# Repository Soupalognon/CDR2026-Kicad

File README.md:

# Robot CDF 2026

Carte électronique principale du robot **Wall-A**, conçu pour la **Coupe de France de Robotique 2026**.

## Description

Ce PCB regroupe tout ce dont le robot a besoin pour fonctionner :

- **Alimentation** : génère les rails 24 V, 12 V, 5 V et 3,3 V à partir de la batterie
- **Moteurs et actionneurs** : commande des moteurs des roues, des moteurs secondaires et des servomoteurs
- **Capteurs** : encodeurs, capteurs de distance, interrupteurs et sondes de température
- **Contrôle bas niveau** : un microcontrôleur STM32F407 pilote le tout en temps réel
- **Liaison avec le PC embarqué** : USB et Ethernet pour le haut niveau. La prise USB Type-C du PC embarqué est une **sortie d'alimentation 5 V**

### Alimentation

La carte est alimentée par la batterie (LiPo 4S 14.8V, connecteur XT90) avec une tension d'entrée de 16 V à 24 V. Elle génère cinq rails avec trois types de convertisseurs :

| Rail | Type de convertisseur | Composant | Courant | Utilisation |
|---|---|---|---|---|
| 24 V | Élévateur (boost) | Module DC/DC ABB ABXS005 | 5,4 A | Moteurs des roues |
| 12 V | Abaisseur (buck) | TI PTN78020W | 5,8 A | Actionneurs (servomoteurs, ...) |
| 5 V actionneurs | Abaisseur (buck) | TI PTN78060W | 3,5 A | Actionneurs (servomoteurs, pompes, canon, télémètres, Lidar, ...) |
| 5 V calcul | Abaisseur (buck) | TI PTN78060W | 3,5 A | PC embarqué et µC |
| 3,3 V | Régulateur linéaire (LDO) | TI TLV75533P | | Logique du µC |

Les rails 24 V, 12 V et 5 V sont réglables par potentiomètre. Les rails 24 V, 12 V et 5 V actionneurs peuvent être activés par le µC. Les rails 5 V et 12 V sont aussi disponibles en sortie sur connecteurs.

### Contrôleurs moteurs

| Moteurs | Driver | Alimentation | Détails |
|---|---|---|---|
| 2 moteurs principaux (roues) | TI DRV8262, double pont en H | 24 V | Transmotec PD4266-24-17-BFEC, avec encodeurs 5 V |
| 2 moteurs secondaires | ST L298N, double pont en H | 5 V ou 12 V | 2 A maximum en continu par moteur |
| 4 servomoteurs AX12/AX18 | Bus série half-duplex (UART) avec adaptation de niveau 3,3 V / 5 V | 12 V | |
| 4 servomoteurs PWM | Signal PWM direct du µC | 5 V ou 12 V | |

Le µC mesure le courant des deux drivers et la température sous chacun d'eux.

### Capteurs

| Capteur | Quantité | Interface | Détails |
|---|---|---|---|
| Encodeurs | 2 | 5 V | Gauche et droite |
| Capteurs de distance Pulse Width | 4 | Largeur d'impulsion | |
| Capteurs de distance analogiques | 4 | ADC, 0 - 3,3 V | |
| Interrupteurs | 4 | Tout ou rien (on/off) | |
| Sondes de température internes | 3 | Thermistances CTN, ADC | Sous le driver moteur principal, sous le driver moteur secondaire, près des alimentations 12 V et 24 V |

### Communications et debug

| Interface | Détails | Utilisation |
|---|---|---|
| USB FS 12 Mb/s | Connecteur USB Type-C | PC embarqué. Cette prise est aussi une **sortie d'alimentation 5 V** |
| Ethernet 100 Mb/s | PHY LAN8742A + RJ45 | PC embarqué |
| UART 115 kbaud | FT231XS (USB-UART) sur micro-USB | Debug |
| Pin headers | Toutes les broches du µC | Accès direct au µC |
| LEDs | 5 LEDs connectées au µC | Debug |

### Informations générales

Le firmware du microcontrôleur est dans le dépôt [CDR2026-Software](https://github.com/Soupalognon/CDR2026-Software).

|  |  |
|---|---|
| Version | v1.0 (septembre 2025) |
| Dimensions | 170 × 100 mm |
| PCB | 4 couches, 1,6 mm |
| Logiciel | KiCad 9 |
| Auteurs | GDU, THO |

## Images

| Dessus | Dessous |
|:---:|:---:|
|  |  |
|  |  |

## Composants principaux

| Fonction | Composant |
|---|---|
| Microcontrôleur | STM32F407IGT6 |
| Alimentation 24V | Module DC/DC ABB ABXS005 |
| Alimentation 12V | TI PTN78020W |
| Alimentations 5V (calcul et actionneurs) | 2 × TI PTN78060W |
| Alimentation 3,3V | TI TLV75533P |
| Driver moteurs principaux | TI DRV8262 |
| Driver moteurs secondaires | ST L298N |
| Ethernet | PHY LAN8742A + transformateur H1102NL + RJ45 |
| USB PC embarqué | Connecteur USB Type-C |
| Debug | FT231XS (USB-UART) sur micro-USB |

La liste complète est dans la BOM : [Robot WallA.xlsx](Robot%20WallA/_output/Robot%20WallA.xlsx).

## Organisation du projet

Le schéma est hiérarchique : la feuille racine contient quatre blocs, eux-mêmes découpés en sous-feuilles.

| Bloc | Sous-feuilles |
|---|---|
| `Power` | `Power_Boost_24V`, `Power_Buck_12V`, `Power_Buck_5V_Actuators`, `Power_Buck_5V_Compute` |
| `MCU` | `MCU_Core`, `MCU_Config`, `MCU_Debug`, `MCU_GPIO`, `MCU_Peripherals` |
| `Motor` | `Motor_WheelDriver`, `Motor_Actuators`, `Motor_Encoders` |
| `Sensors` | |

```
.
├── .images/                 Captures du PCB utilisées dans ce README
├── Docs/                    Documents de référence et configuration de commande JLCPCB
├── Robot WallA/             Projet KiCad
│   ├── Robot WallA.kicad_pro / .kicad_sch / .kicad_pcb
│   ├── _Libraries/          Symboles, empreintes et modèles 3D spécifiques
│   └── _output/             Fichiers de fabrication
│       ├── Fab/ et Fab.zip      Gerbers et perçages
│       ├── Robot WallA.pdf      Schéma
│       ├── Robot WallA.xlsx     BOM
│       └── ibom.html            BOM interactive
├── LICENSE
└── README.md
```

## Fabrication

Les fichiers de fabrication sont dans [Robot WallA/_output](Robot%20WallA/_output). La commande a été faite chez JLCPCB, les réglages utilisés sont dans [Docs](Docs). Le dossier contient aussi la configuration du stencil.

Le dossier [Docs](Docs) contient aussi le schéma de la carte STM32F4 Discovery ([MB1137](Docs/MB1137.pdf)), qui sert de référence pour la partie microcontrôleur.

## Licence

Projet sous licence MIT, voir [LICENSE](LICENSE).

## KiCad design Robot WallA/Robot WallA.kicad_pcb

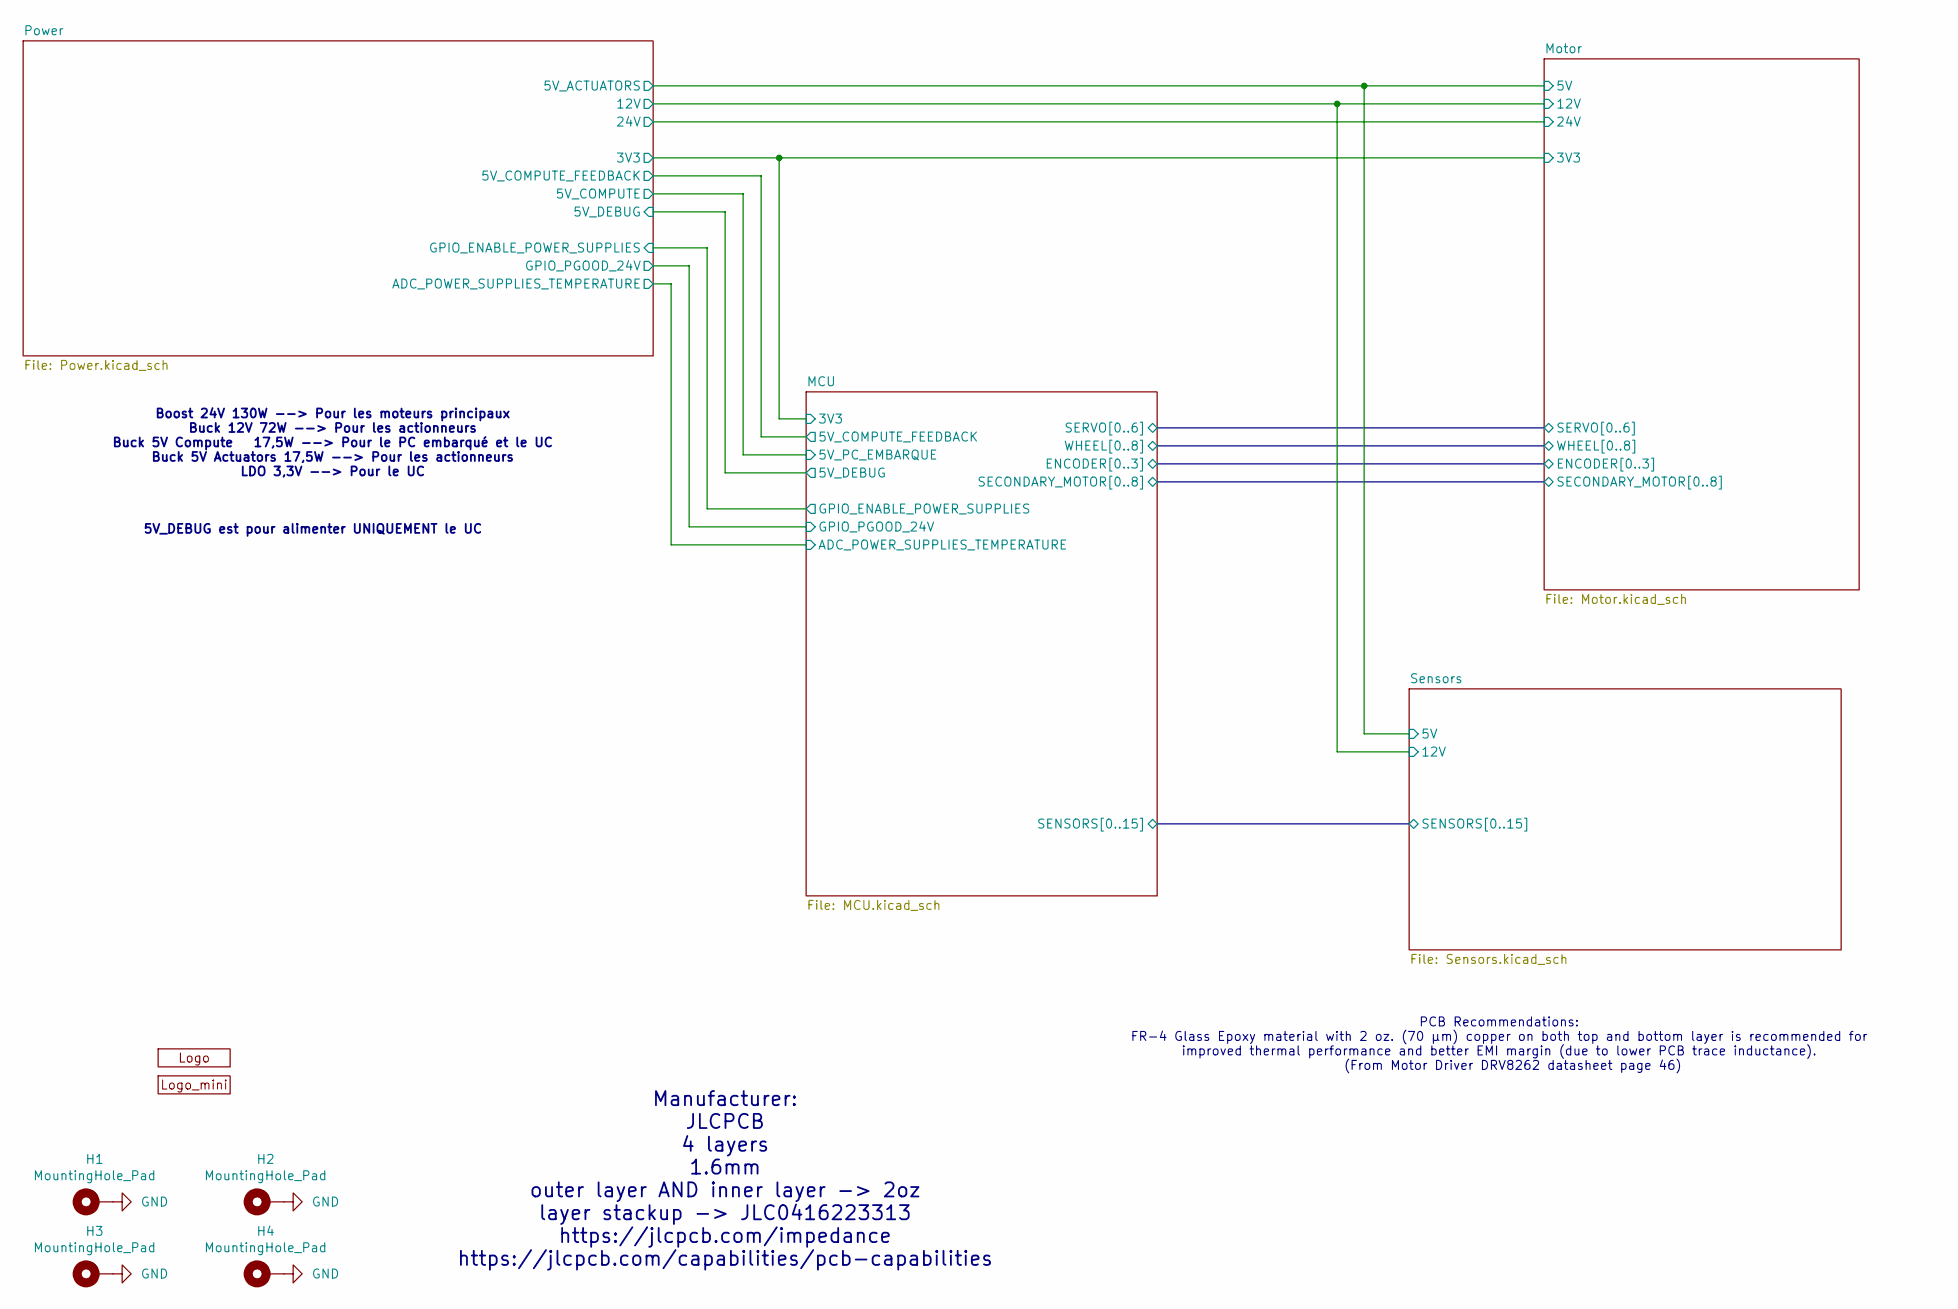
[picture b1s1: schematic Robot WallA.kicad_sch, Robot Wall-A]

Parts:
H1, H2, H3, H4: MountingHole_Pad; MountingHole_4.3mm_M4_DIN965_Pad_TopBottom
U11: Logo_Wall-A
U12: Logo_mini_Wall-A

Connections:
GND: H1.1, H2.1, H3.1, H4.1; also elsewhere on the board

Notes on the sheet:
5V_DEBUG est pour alimenter UNIQUEMENT le UC
PCB Recommendations: FR-4 Glass Epoxy material with 2 oz. (70 μm) copper on both top and bottom layer is recommended for improved thermal performance and better EMI margin (due to lower PCB trace inductance). (From Motor Driver DRV8262 datasheet page 46)
Boost 24V 130W --> Pour les moteurs principaux Buck 12V 72W --> Pour les actionneurs Buck 5V Compute 17,5W --> Pour le PC embarqué et le UC Buck 5V Actuators 17,5W --> Pour les actionneurs LDO 3,3V --> Pour le UC
Manufacturer: JLCPCB 4 layers 1.6mm outer layer AND inner layer -> 2oz layer stackup -> JLC0416223313 https://jlcpcb.com/impedance https://jlcpcb.com/capabilities/pcb-capabilities

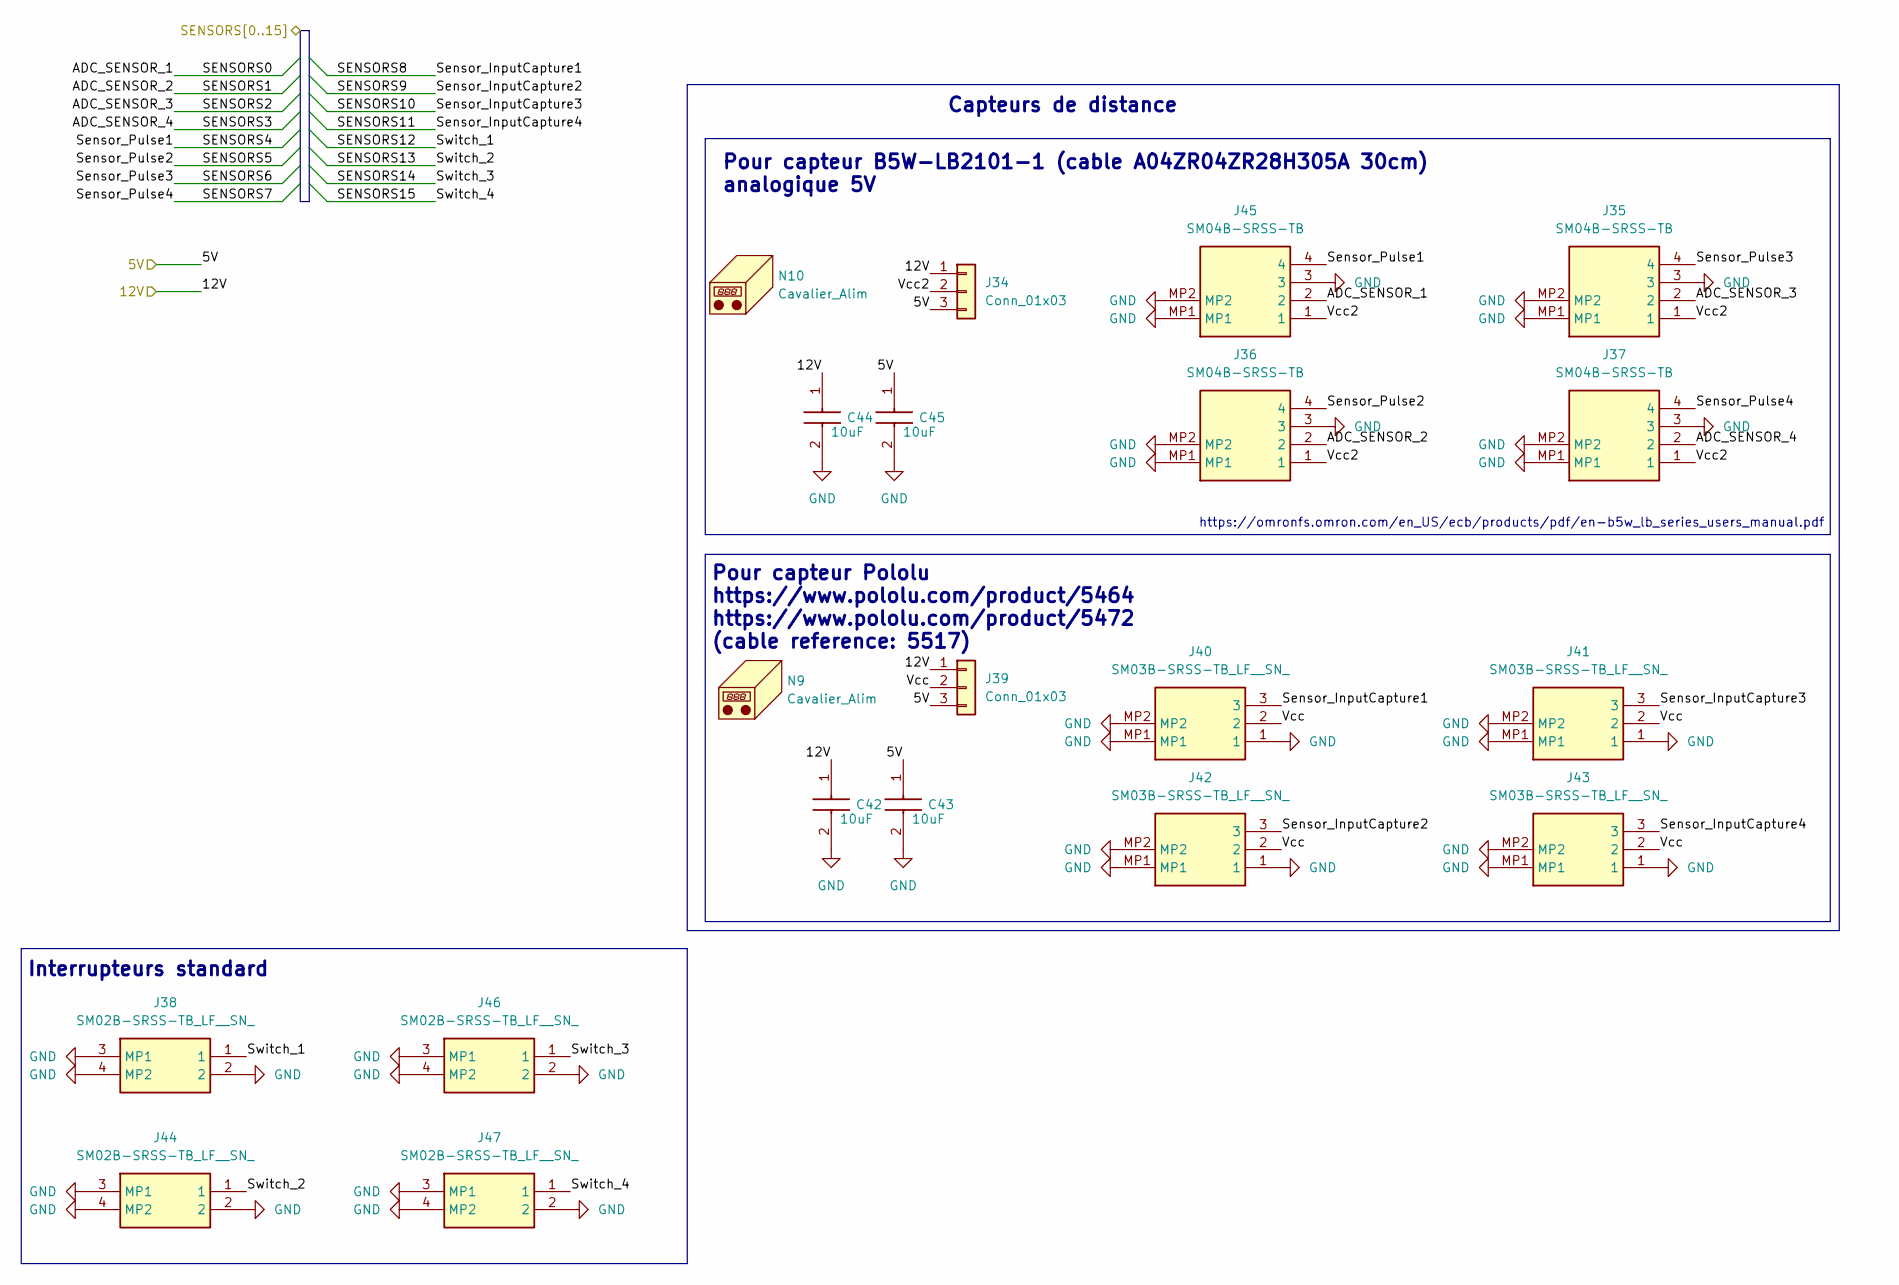
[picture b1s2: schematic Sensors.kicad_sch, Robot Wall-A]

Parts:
C42, C43, C44, C45: 10uF; C_0603_1608Metric_Pad1.08x0.95mm_HandSolder; Manufacturer_Part_Number CL10A106MA8NRNC
J34, J39: Conn_01x03; PinHeader_1x03_P2.54mm_Vertical
J35, J36, J37, J45: SM04B-SRSS-TB; SM04BSRSSTB; Manufacturer_Part_Number SM04B-SRSS-TB
J38, J44, J46, J47: SM02B-SRSS-TB_LF__SN_; SM02BSRSSTBLFSN; Manufacturer_Part_Number SM02B-SRSS-TB(LF)(SN); Mouser Part Number N/A
J40, J41, J42, J43: SM03B-SRSS-TB_LF__SN_; SM03BSRSSTBLFSN; Manufacturer_Part_Number SM03B-SRSS-TB(LF)(SN); Mouser Part Number N/A
N9, N10: Cavalier_Alim; Manufacturer_Part_Number 15-29-1024

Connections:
/MCU/SENSORS0: J45.2; also elsewhere on the board
/MCU/SENSORS1: J36.2; also elsewhere on the board
/MCU/SENSORS2: J35.2; also elsewhere on the board
/MCU/SENSORS3: J37.2; also elsewhere on the board
/MCU/SENSORS4: J45.4; also elsewhere on the board
/MCU/SENSORS5: J36.4; also elsewhere on the board
/MCU/SENSORS6: J35.4; also elsewhere on the board
/MCU/SENSORS7: J37.4; also elsewhere on the board
/MCU/SENSORS8: J40.3; also elsewhere on the board
/MCU/SENSORS9: J42.3; also elsewhere on the board
/MCU/SENSORS10: J41.3; also elsewhere on the board
/MCU/SENSORS11: J43.3; also elsewhere on the board
/MCU/SENSORS12: J38.1; also elsewhere on the board
/MCU/SENSORS13: J44.1; also elsewhere on the board
/MCU/SENSORS14: J46.1; also elsewhere on the board
/MCU/SENSORS15: J47.1; also elsewhere on the board
/Motor/5V: C43.1, C45.1, J34.3, J39.3; also elsewhere on the board
/Power/12V: C42.1, C44.1, J34.1, J39.1; also elsewhere on the board
/Sensors/Vcc: J39.2, J40.2, J41.2, J42.2, J43.2
/Sensors/Vcc2: J34.2, J35.1, J36.1, J37.1, J45.1
GND: C42.2, C43.2, C44.2, C45.2, J35.3, J35.MP1, J35.MP2, J36.3, J36.MP1, J36.MP2, J37.3, J37.MP1, J37.MP2, J38.2, J38.3 (MP1), J38.4 (MP2), J40.1, J40.MP1, J40.MP2, J41.1, J41.MP1, J41.MP2, J42.1, J42.MP1, J42.MP2, J43.1, J43.MP1, J43.MP2, J44.2, J44.3 (MP1), J44.4 (MP2), J45.3, J45.MP1, J45.MP2, J46.2, J46.3 (MP1), J46.4 (MP2), J47.2, J47.3 (MP1), J47.4 (MP2); also elsewhere on the board

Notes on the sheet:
Pour capteur Pololu https://www.pololu.com/product/5464 https://www.pololu.com/product/5472 (cable reference: 5517)
Interrupteurs standard
Pour capteur B5W-LB2101-1 (cable A04ZR04ZR28H305A 30cm) analogique 5V
Capteurs de distance
https://omronfs.omron.com/en_US/ecb/products/pdf/en-b5w_lb_series_users_manual.pdf

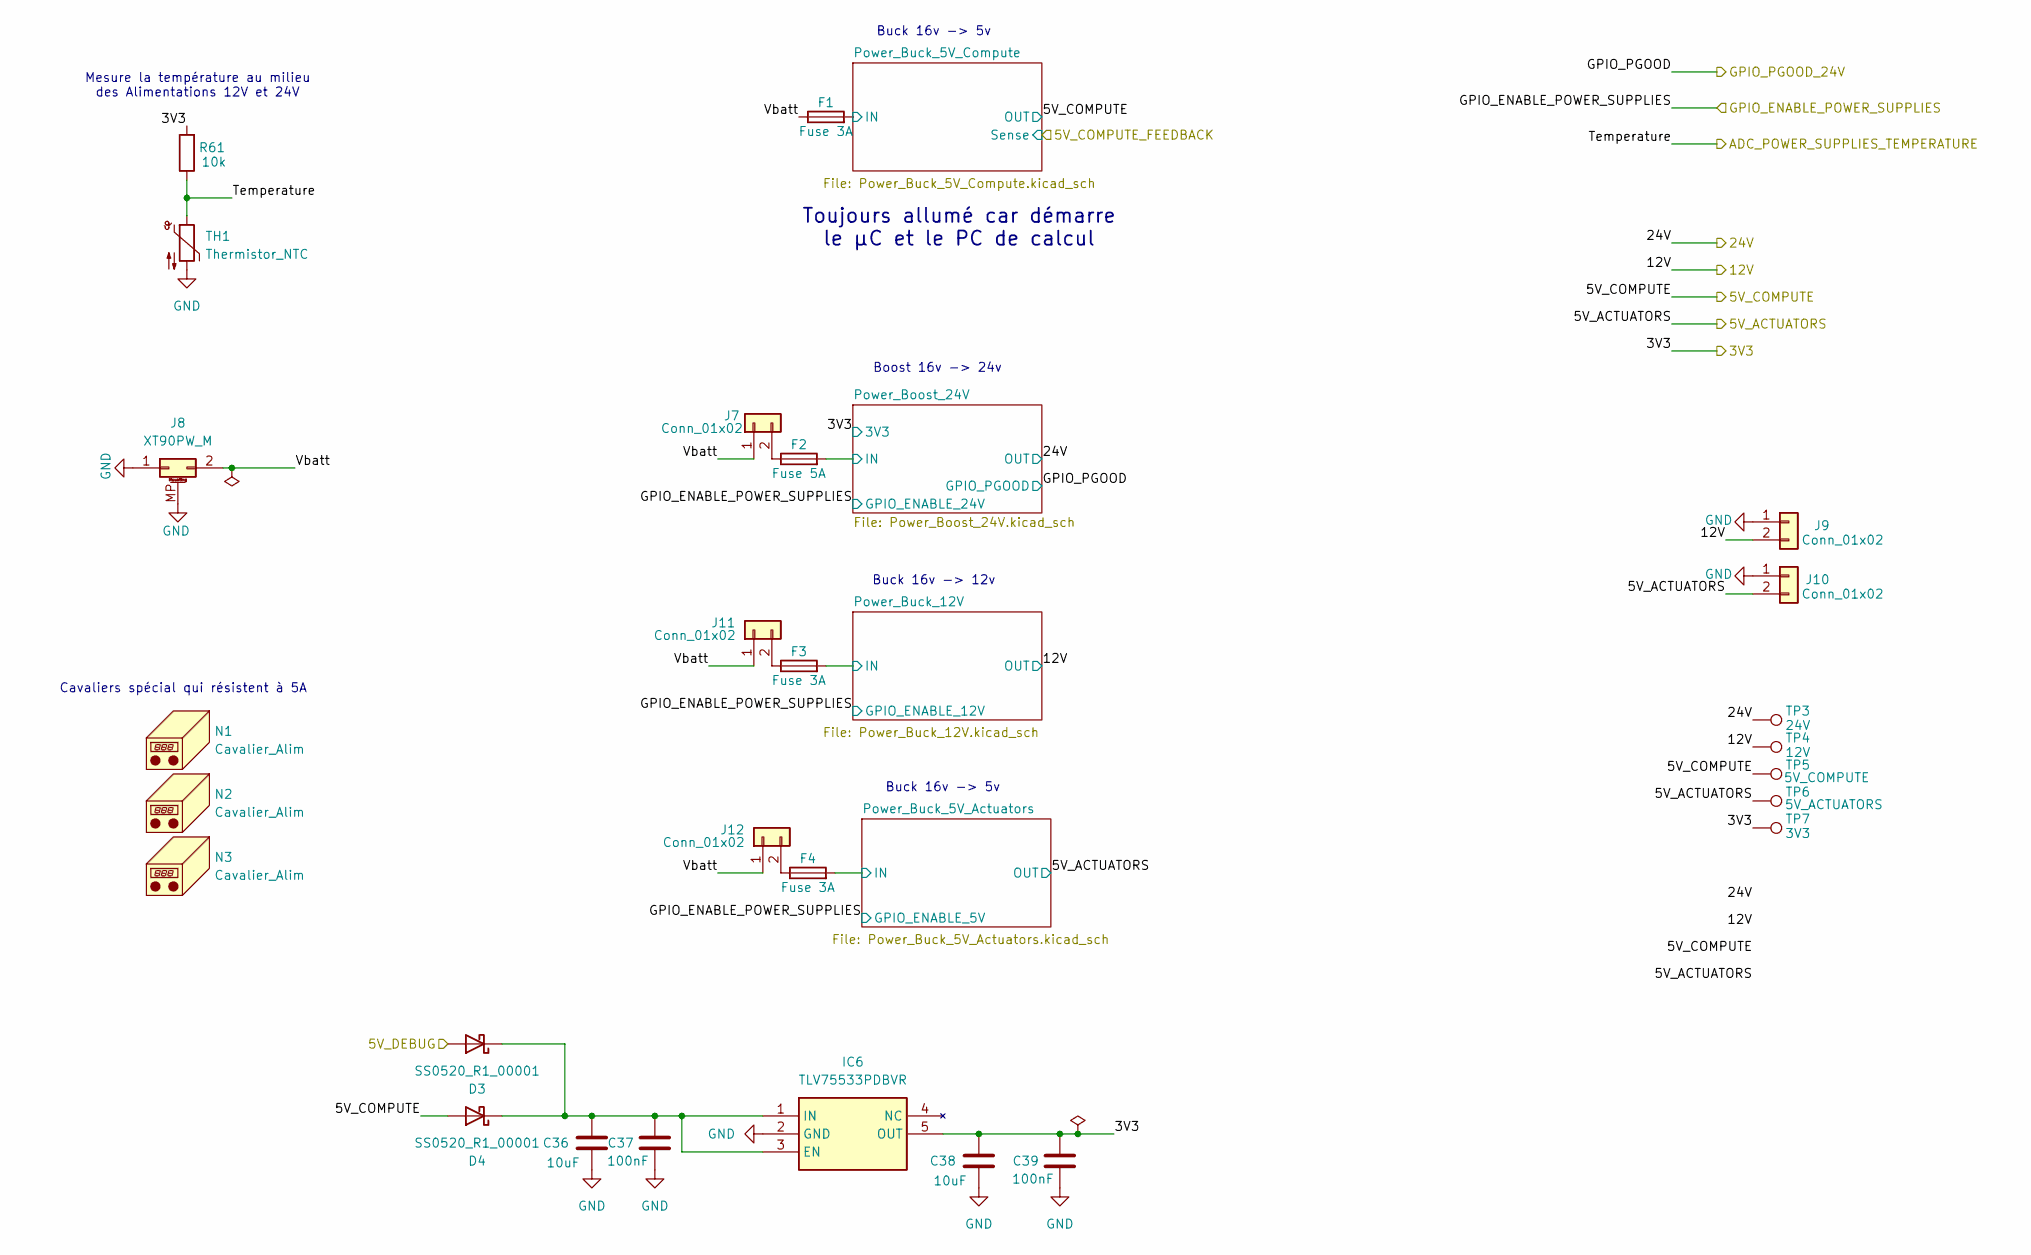
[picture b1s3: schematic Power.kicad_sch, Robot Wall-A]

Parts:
C36, C38: 10uF; C_0603_1608Metric_Pad1.08x0.95mm_HandSolder; Manufacturer_Part_Number CL10A106MA8NRNC
C37, C39: 100nF; C_0603_1608Metric_Pad1.08x0.95mm_HandSolder; Manufacturer_Part_Number KGM15BR71H104KT
D3, D4: SS0520_R1_00001; D_SOD-123; Manufacturer_Part_Number SS0520_R1_00001
F1, F3, F4: Fuse 3A; Fuse_1206_3216Metric; Manufacturer_Part_Number JB12F3001R
F2: Fuse 5A; Fuse_1206_3216Metric; Manufacturer_Part_Number JB12S5001R
IC6: TLV75533PDBVR; SOT95P280X145-5N; Manufacturer_Part_Number TLV75533PDBVR
J7, J11, J12: Conn_01x02; PinHeader_1x02_P2.54mm_Vertical
J8: XT90PW_M; AMASS_XT90PW-M_1x02_P10.90mm_Horizontal; Manufacturer_Part_Number XT90PW-M
J9, J10: Conn_01x02; SHDR2W50P0X200_1X2_590X450X600P; Manufacturer_Part_Number B2B-PH-K-S(LF)(SN)
N1, N2, N3: Cavalier_Alim; Manufacturer_Part_Number 15-29-1024
R61: 10k; R_0603_1608Metric_Pad0.98x0.95mm_HandSolder; Manufacturer_Part_Number 667-ERJ-3GEYJ103V
TH1: Thermistor_NTC; R_0603_1608Metric_Pad0.98x0.95mm_HandSolder; Manufacturer_Part_Number NCU18XH103E60RB
TP3: 24V; TestPoint_Pad_D2.0mm
TP4: 12V; TestPoint_Pad_D2.0mm
TP5: 5V_COMPUTE; TestPoint_Pad_D2.0mm
TP6: 5V_ACTUATORS; TestPoint_Pad_D2.0mm
TP7: 3V3; TestPoint_Pad_D2.0mm

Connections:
/MCU/3V3: C38.1, C39.1, IC6.5 (OUT), R61.2, TP7.1; also elsewhere on the board
/MCU/5V_PC_EMBARQUE: D4.2 (A), TP5.1; also elsewhere on the board
/MCU/MCU_Debug/5V_DEBUG: D3.2 (A); also elsewhere on the board
/Motor/5V: J10.2, TP6.1; also elsewhere on the board
/Power/12V: J9.2, TP4.1; also elsewhere on the board
/Power/24V: TP3.1; also elsewhere on the board
/Power/Power_Boost_24V/IN: F2.2; also elsewhere on the board
/Power/Power_Buck_5V_Actuators/IN: F4.2; also elsewhere on the board
/Power/Power_Buck_5V_Compute/IN: F1.2; also elsewhere on the board
/Power/Power_Buck_12V/IN: F3.2; also elsewhere on the board
/Power/Temperature: R61.1, TH1.1; also elsewhere on the board
/Power/Vbatt: F1.1, J7.1, J8.2, J11.1, J12.1
GND: C36.2, C37.2, C38.2, C39.2, IC6.2 (GND), J8.1, J8.MP (MountPin), J9.1, J10.1, TH1.2; also elsewhere on the board
unnamed: C36.1, C37.1, D3.1 (K), D4.1 (K), IC6.1 (IN), IC6.3 (EN)
unnamed: F2.1, J7.2
unnamed: F3.1, J11.2
unnamed: F4.1, J12.2

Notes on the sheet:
Cavaliers spécial qui résistent à 5A
Buck 16v -> 12v
Mesure la température au milieu des Alimentations 12V et 24V
Toujours allumé car démarre le µC et le PC de calcul
Boost 16v -> 24v
Buck 16v -> 5v

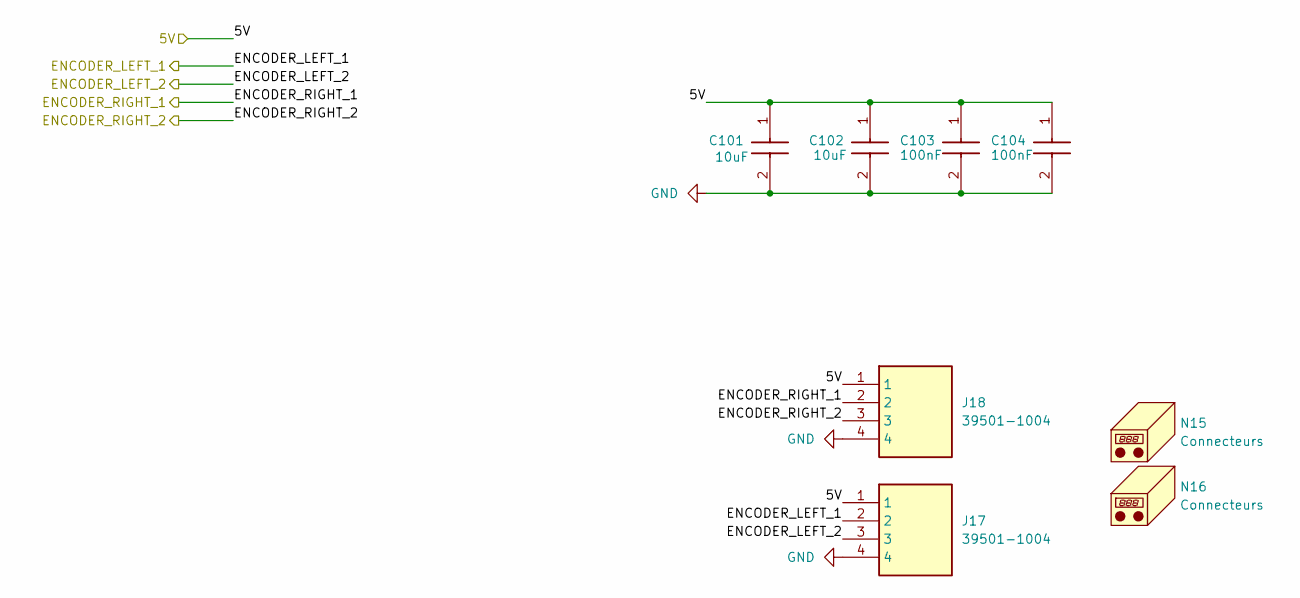
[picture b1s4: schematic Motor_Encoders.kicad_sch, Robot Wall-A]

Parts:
C101, C102: 10uF; C_0603_1608Metric_Pad1.08x0.95mm_HandSolder; Manufacturer_Part_Number CL10A106MA8NRNC
C103, C104: 100nF; C_0603_1608Metric_Pad1.08x0.95mm_HandSolder; Manufacturer_Part_Number KGM15BR71H104KT
J17, J18: 39501-1004; 395011004; Manufacturer_Part_Number 39501-1004
N15, N16: Connecteurs; Manufacturer_Part_Number 39503-2004

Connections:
/MCU/ENCODER0: J18.2; also elsewhere on the board
/MCU/ENCODER1: J18.3; also elsewhere on the board
/MCU/ENCODER2: J17.2; also elsewhere on the board
/MCU/ENCODER3: J17.3; also elsewhere on the board
/Motor/5V: C101.1, C102.1, C103.1, C104.1, J17.1, J18.1; also elsewhere on the board
GND: C101.2, C102.2, C103.2, C104.2, J17.4, J18.4; also elsewhere on the board

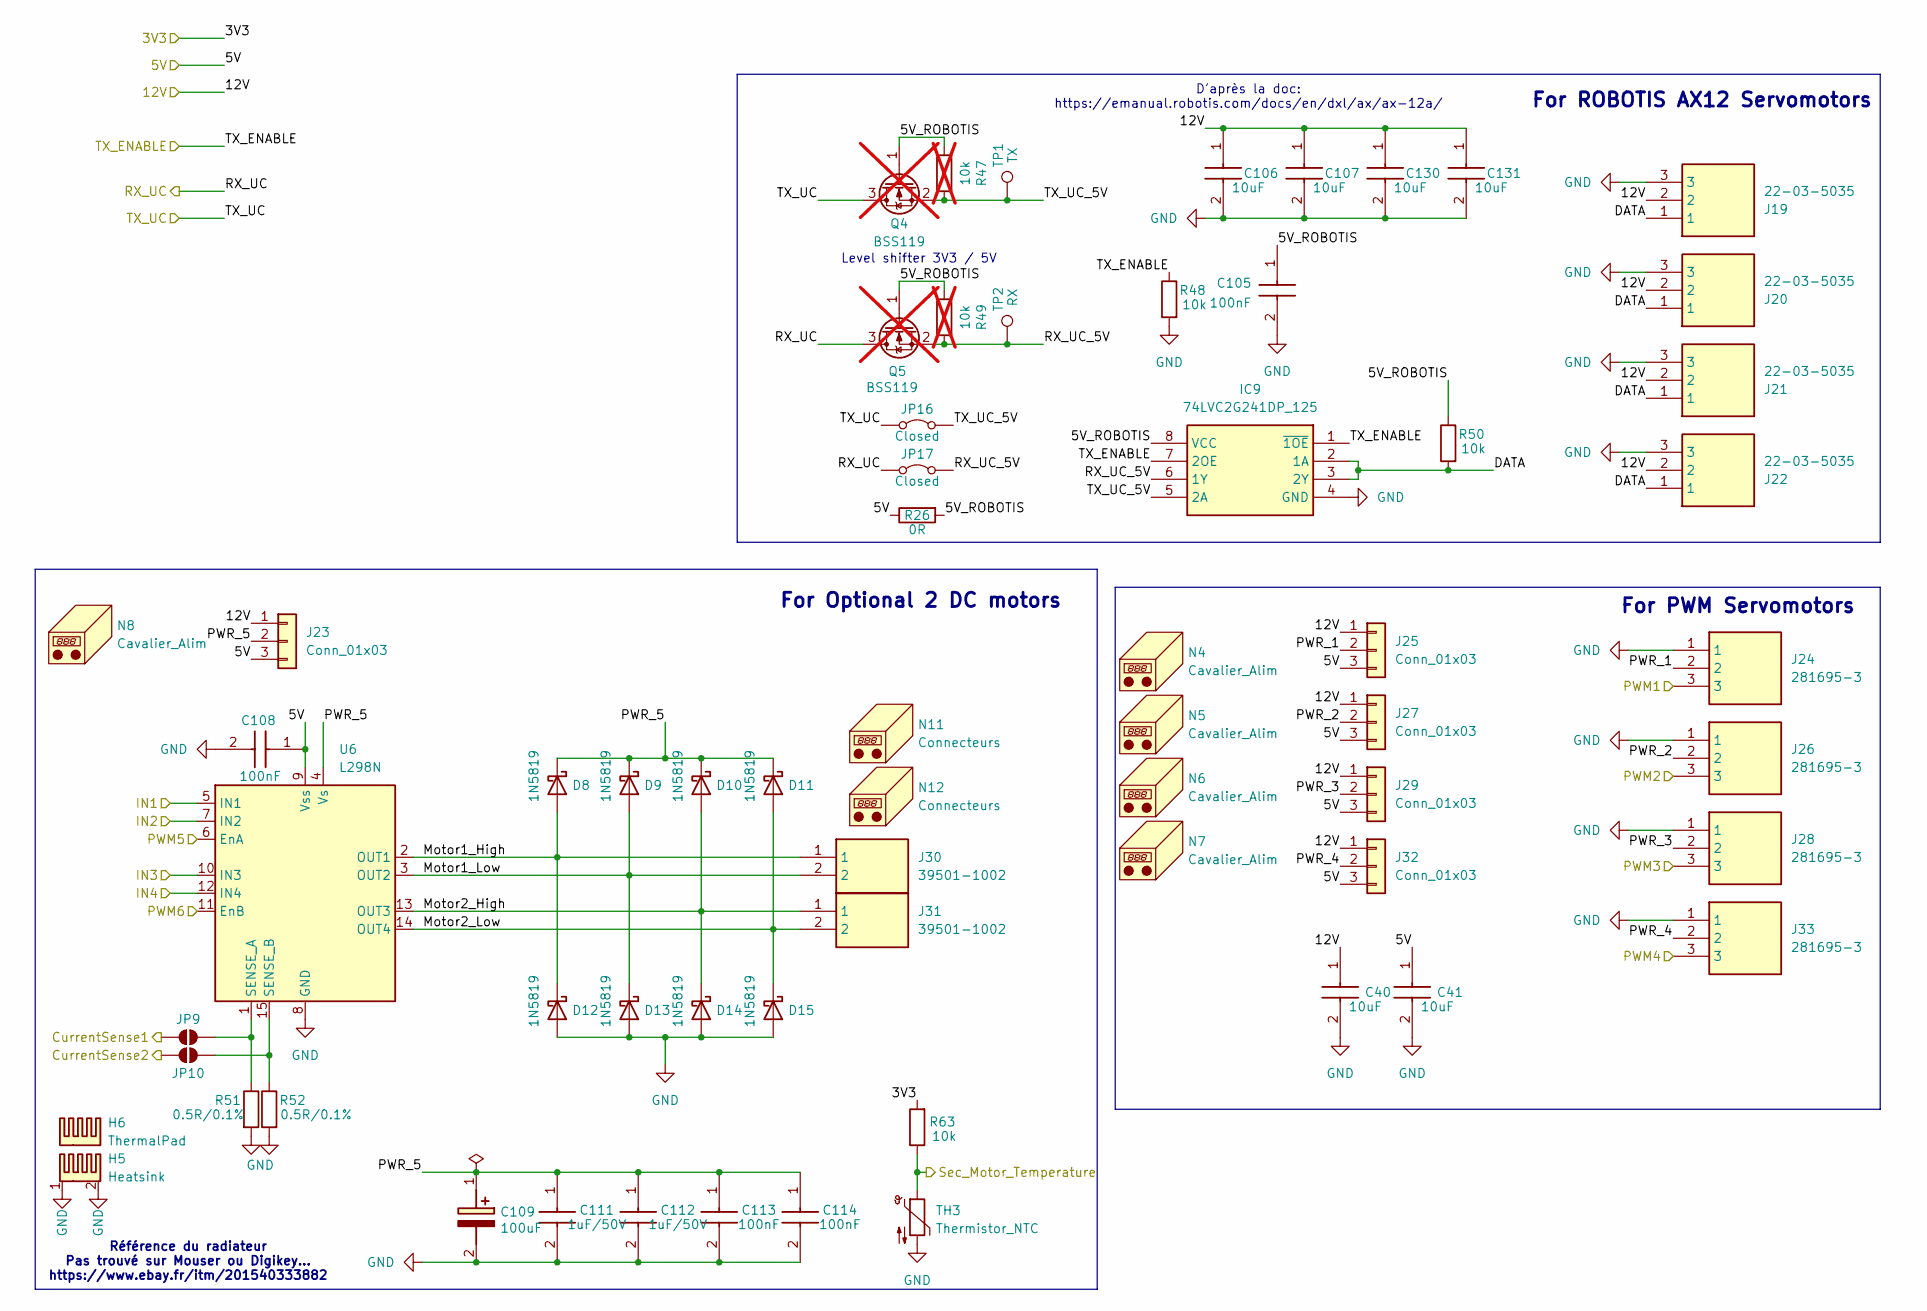
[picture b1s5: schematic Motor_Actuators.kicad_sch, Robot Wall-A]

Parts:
C40, C41, C106, C107, C130, C131: 10uF; C_0603_1608Metric_Pad1.08x0.95mm_HandSolder; Manufacturer_Part_Number CL10A106MA8NRNC
C105, C108, C113, C114: 100nF; C_0603_1608Metric_Pad1.08x0.95mm_HandSolder; Manufacturer_Part_Number KGM15BR71H104KT
C109: 100uF; CAPAE830X1050N; Manufacturer_Part_Number EDK107M050A9MAA
C111, C112: 1uF/50V; C_0603_1608Metric_Pad1.08x0.95mm_HandSolder; Manufacturer_Part_Number CL10A105KB8NNNC
D8, D9, D10, D11, D12, D13, D14, D15: 1N5819; D_SOD-123; Manufacturer_Part_Number 1N5819HW-7-F
H5: Heatsink; 64710ABEP; Manufacturer_Part_Number 647-10ABEP
H6: ThermalPad; Manufacturer_Part_Number SPA2000-0.015-AC-62
IC9: 74LVC2G241DP_125; SOP65P400X110-8N; Manufacturer_Part_Number 74LVC2G241DP_125
J19, J20, J21, J22: 22-03-5035; SHDR3W60P0X250_1X3_990X490X590P; Manufacturer_Part_Number '22-03-5035
J23, J25, J27, J29, J32: Conn_01x03; PinHeader_1x03_P2.54mm_Vertical
J24, J26, J28, J33: 281695-3; SHDR3W65P0X254_1X3_762X508X1150P; Manufacturer_Part_Number 281695-3
J30, J31: 39501-1002; 395011002; Manufacturer_Part_Number 39501-1002
JP9, JP10: SolderJumper; SolderJumper-2_P1.3mm_Open_Pad1.0x1.5mm
JP16, JP17: Closed; SolderJumper-2_P1.3mm_Bridged_RoundedPad1.0x1.5mm
N4, N5, N6, N7, N8: Cavalier_Alim; Manufacturer_Part_Number 15-29-1024
N11, N12: Connecteurs; Manufacturer_Part_Number 39503-2002
Q4, Q5: BSS119; SOT95P260X110-3N; Manufacturer_Part_Number BSS119NH6327XTSA1; not fitted
R26: 0R; R_0603_1608Metric_Pad0.98x0.95mm_HandSolder
R47, R49: 10k; R_0603_1608Metric_Pad0.98x0.95mm_HandSolder; Manufacturer_Part_Number 667-ERJ-3GEYJ103V; not fitted
R48, R50, R63: 10k; R_0603_1608Metric_Pad0.98x0.95mm_HandSolder; Manufacturer_Part_Number 667-ERJ-3GEYJ103V
R51, R52: 0.5R/0.1%; R_0603_1608Metric_Pad0.98x0.95mm_HandSolder; Manufacturer_Part_Number CSR0603FKR500
TH3: Thermistor_NTC; R_0603_1608Metric_Pad0.98x0.95mm_HandSolder; Manufacturer_Part_Number NCU18XH103E60RB
TP1: TX; TestPoint_Pad_D1.0mm
TP2: RX; TestPoint_Pad_D1.0mm
U6: L298N; TO-220-15_P2.54x5.08mm_StaggerOdd_Lead4.58mm_Vertical; Manufacturer_Part_Number L298N

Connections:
/MCU/3V3: R63.2; also elsewhere on the board
/MCU/SECONDARY_MOTOR0: JP9.1 (A); also elsewhere on the board
/MCU/SECONDARY_MOTOR1: JP10.1 (A); also elsewhere on the board
/MCU/SECONDARY_MOTOR2: U6.5 (IN1); also elsewhere on the board
/MCU/SECONDARY_MOTOR3: U6.7 (IN2); also elsewhere on the board
/MCU/SECONDARY_MOTOR4: U6.10 (IN3); also elsewhere on the board
/MCU/SECONDARY_MOTOR5: U6.12 (IN4); also elsewhere on the board
/MCU/SECONDARY_MOTOR6: U6.6 (EnA); also elsewhere on the board
/MCU/SECONDARY_MOTOR7: U6.11 (EnB); also elsewhere on the board
/MCU/SECONDARY_MOTOR8: R63.1, TH3.1; also elsewhere on the board
/MCU/SERVO0: JP17.1 (A), Q5.3; also elsewhere on the board
/MCU/SERVO1: JP16.1 (A), Q4.3; also elsewhere on the board
/MCU/SERVO2: IC9.1 (~1OE), IC9.7 (2OE), R48.1; also elsewhere on the board
/MCU/SERVO3: J24.3; also elsewhere on the board
/MCU/SERVO4: J26.3; also elsewhere on the board
/MCU/SERVO5: J28.3; also elsewhere on the board
/MCU/SERVO6: J33.3; also elsewhere on the board
/Motor/5V: C41.1, C108.1, J23.3, J25.3, J27.3, J29.3, J32.3, R26.1, U6.9 (Vss); also elsewhere on the board
/Motor/Motor_Actuators/5V_ROBOTIS: C105.1, IC9.8 (VCC), Q4.1, Q5.1, R26.2, R47.1, R49.1, R50.1
/Motor/Motor_Actuators/DATA: IC9.2 (1A), IC9.3 (2Y), J19.1, J20.1, J21.1, J22.1, R50.2
/Motor/Motor_Actuators/Motor1_High: D8.2 (A), D12.1 (K), J30.1, U6.2 (OUT1)
/Motor/Motor_Actuators/Motor1_Low: D9.2 (A), D13.1 (K), J30.2, U6.3 (OUT2)
/Motor/Motor_Actuators/Motor2_High: D10.2 (A), D14.1 (K), J31.1, U6.13 (OUT3)
/Motor/Motor_Actuators/Motor2_Low: D11.2 (A), D15.1 (K), J31.2, U6.14 (OUT4)
/Motor/Motor_Actuators/PWR_1: J24.2, J25.2
/Motor/Motor_Actuators/PWR_2: J26.2, J27.2
/Motor/Motor_Actuators/PWR_3: J28.2, J29.2
/Motor/Motor_Actuators/PWR_4: J32.2, J33.2
/Motor/Motor_Actuators/PWR_5: C109.1 (+), C111.1, C112.1, C113.1, C114.1, D8.1 (K), D9.1 (K), D10.1 (K), D11.1 (K), J23.2, U6.4 (Vs)
/Motor/Motor_Actuators/RX_UC_5V: IC9.6 (1Y), JP17.2 (B), Q5.2, R49.2, TP2.1
/Motor/Motor_Actuators/TX_UC_5V: IC9.5 (2A), JP16.2 (B), Q4.2, R47.2, TP1.1
/Power/12V: C40.1, C106.1, C107.1, C130.1, C131.1, J19.2, J20.2, J21.2, J22.2, J23.1, J25.1, J27.1, J29.1, J32.1; also elsewhere on the board
GND: C40.2, C41.2, C105.2, C106.2, C107.2, C108.2, C109.2 (-), C111.2, C112.2, C113.2, C114.2, C130.2, C131.2, D12.2 (A), D13.2 (A), D14.2 (A), D15.2 (A), H5.1, H5.2, IC9.4 (GND), J19.3, J20.3, J21.3, J22.3, J24.1, J26.1, J28.1, J33.1, R48.2, R51.2, R52.2, TH3.2, U6.8 (GND); also elsewhere on the board
unnamed: JP9.2 (B), R51.1, U6.1 (SENSE_A)
unnamed: JP10.2 (B), R52.1, U6.15 (SENSE_B)

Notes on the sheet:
D'après la doc: https://emanual.robotis.com/docs/en/dxl/ax/ax-12a/
Référence du radiateur Pas trouvé sur Mouser ou Digikey... https://www.ebay.fr/itm/201540333882
For ROBOTIS AX12 Servomotors
For Optional 2 DC motors
Level shifter 3V3 / 5V
For PWM Servomotors
